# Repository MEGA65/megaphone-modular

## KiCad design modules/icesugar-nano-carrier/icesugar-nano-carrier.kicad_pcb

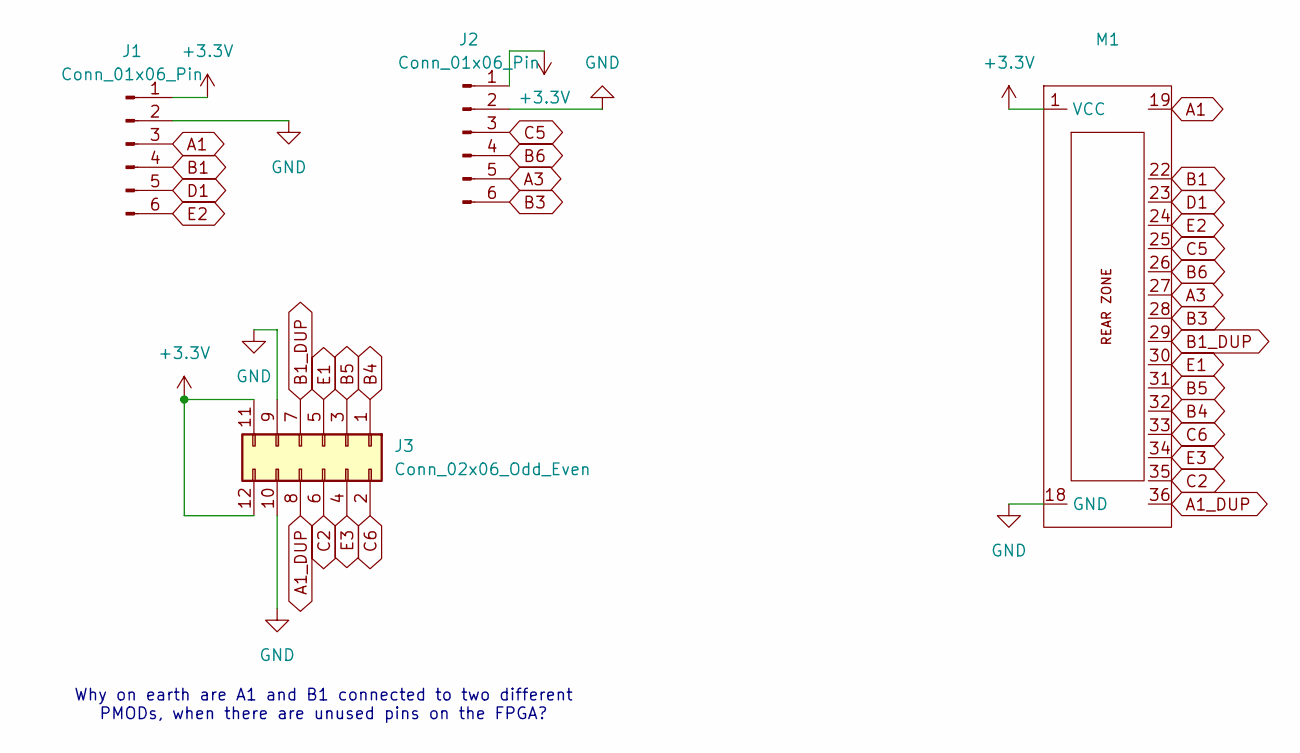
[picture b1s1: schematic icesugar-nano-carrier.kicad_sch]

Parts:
J1, J2: Conn_01x06_Pin; PinHeader_1x06_P2.54mm_Vertical
J3: Conn_02x06_Odd_Even; PinHeader_2x06_P2.54mm_Vertical
M1: MegaCastle2x18-Module-I24.0x40.9-M800067FFF

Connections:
+3.3V: J1.1, J2.1, J3.11, J3.12, M1.1 (VCC)
A1: J1.3, M1.19
A1_DUP: J3.8, M1.36
A3: J2.5, M1.27
B1: J1.4, M1.22
B1_DUP: J3.7, M1.29
B3: J2.6, M1.28
B4: J3.1, M1.32
B5: J3.3, M1.31
B6: J2.4, M1.26
C2: J3.6, M1.35
C5: J2.3, M1.25
C6: J3.2, M1.33
D1: J1.5, M1.23
E1: J3.5, M1.30
E2: J1.6, M1.24
E3: J3.4, M1.34
GND: J1.2, J2.2, J3.9, J3.10, M1.18 (GND)

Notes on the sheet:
Why on earth are A1 and B1 connected to two different PMODs, when there are unused pins on the FPGA?

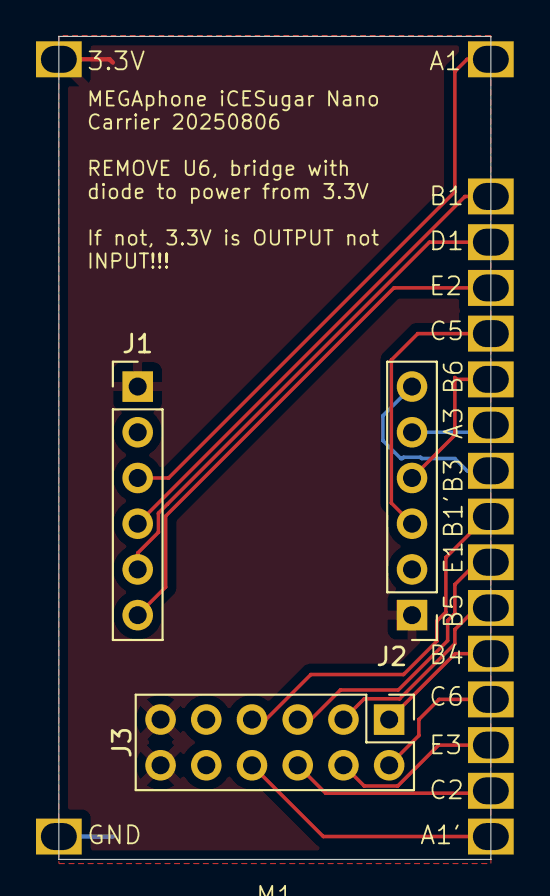
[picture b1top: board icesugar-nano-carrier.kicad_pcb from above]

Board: 2 copper layers, 24.0 x 45.7 mm, 4 parts (0 on the bottom side), 18 nets.

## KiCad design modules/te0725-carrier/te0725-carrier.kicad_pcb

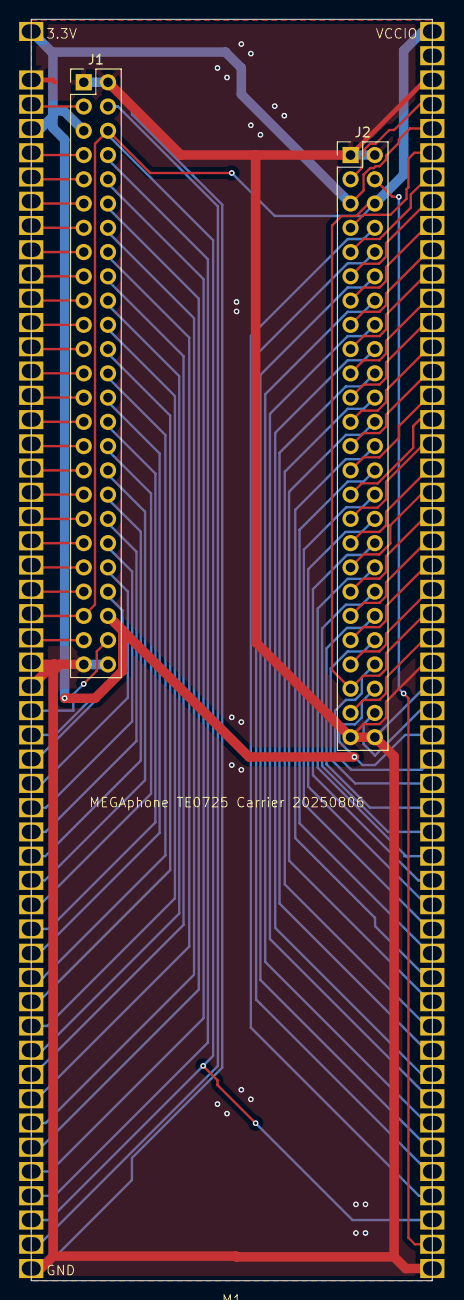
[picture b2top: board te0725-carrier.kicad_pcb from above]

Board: 2 copper layers, 42.0 x 132.1 mm, 3 parts (0 on the bottom side), 87 nets.

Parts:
J1, J2: Conn_02x25_Odd_Even; PinHeader_2x25_P2.54mm_Vertical
M1: MegaCastle2x52-Module-I42.0x127.3-M1

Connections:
J1_1: J1.1, J1.2, J1.49, J1.50, J2.1, J2.2, J2.49, J2.50, M1.3, M1.27, M1.28, M1.52 (GND), M1.55, M1.79, M1.80, M1.104
J1_3: J1.3, M1.4
J1_4: J1.4, M1.51
J1_7: J1.7, M1.6
J1_8: J1.8, M1.49
J1_9: J1.9, M1.7
J1_10: J1.10, M1.48
J1_11: J1.11, M1.8
J1_12: J1.12, M1.47
J1_13: J1.13, M1.9
J1_14: J1.14, M1.46
J1_15: J1.15, M1.10
J1_16: J1.16, M1.45
J1_17: J1.17, M1.11
J1_18: J1.18, M1.44
J1_19: J1.19, M1.12
J1_20: J1.20, M1.43
J1_21: J1.21, M1.13
J1_22: J1.22, M1.42
J1_23: J1.23, M1.14
J1_24: J1.24, M1.41
J1_25: J1.25, M1.15
J1_26: J1.26, M1.40
J1_27: J1.27, M1.16
J1_28: J1.28, M1.39
J1_29: J1.29, M1.17
J1_30: J1.30, M1.38
J1_31: J1.31, M1.18
J1_32: J1.32, M1.37
J1_33: J1.33, M1.19
J1_34: J1.34, M1.36
J1_35: J1.35, M1.20
J1_36: J1.36, M1.35
J1_37: J1.37, M1.21
J1_38: J1.38, M1.34
J1_39: J1.39, M1.22
J1_40: J1.40, M1.33
J1_41: J1.41, M1.23
J1_42: J1.42, M1.32
J1_43: J1.43, M1.24
J1_44: J1.44, M1.31
J1_45: J1.6, J1.45, J2.6, J2.45, M1.25, M1.50, M1.53, M1.77, M1.102
J1_46: J1.5, J1.46, J2.5, J2.46, M1.1 (VCC), M1.5, M1.30, M1.57, M1.82
J1_47: J1.47, M1.26
J1_48: J1.48, M1.29
J2_3: J2.3, M1.56
J2_4: J2.4, M1.103
J2_7: J2.7, M1.58
J2_8: J2.8, M1.101
J2_9: J2.9, M1.59
J2_10: J2.10, M1.100
J2_11: J2.11, M1.60
J2_12: J2.12, M1.99
J2_13: J2.13, M1.61
J2_14: J2.14, M1.98
J2_15: J2.15, M1.62
J2_16: J2.16, M1.97
J2_17: J2.17, M1.63
J2_18: J2.18, M1.96
J2_19: J2.19, M1.64
J2_20: J2.20, M1.95
J2_21: J2.21, M1.65
J2_22: J2.22, M1.94
J2_23: J2.23, M1.66
J2_24: J2.24, M1.93
J2_25: J2.25, M1.67
J2_26: J2.26, M1.92
J2_27: J2.27, M1.68
J2_28: J2.28, M1.91
J2_29: J2.29, M1.69
J2_30: J2.30, M1.90
J2_31: J2.31, M1.70
J2_32: J2.32, M1.89
J2_33: J2.33, M1.71
J2_34: J2.34, M1.88
J2_35: J2.35, M1.72
J2_36: J2.36, M1.87
J2_37: J2.37, M1.73
J2_38: J2.38, M1.86
J2_39: J2.39, M1.74
J2_40: J2.40, M1.85
J2_41: J2.41, M1.75
J2_42: J2.42, M1.84
J2_43: J2.43, M1.76
J2_44: J2.44, M1.83
J2_47: J2.47, M1.78
J2_48: J2.48, M1.81

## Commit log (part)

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2025-08-06 finish te0725 carrier module layout
2025-08-06 add symbols and footprints for ICESugar Nano module
2025-08-06 begin implementing iCESugar Nano carrier module
2025-08-10 begin making unicode string printer.
2025-08-10 display dimensions info for rendered string
2025-08-10 update icesugar project for gerber output
2025-08-10 remove debug stuff
2025-08-10 allow reverse text when rendering UTF8 strings
2025-08-10 reinstant use of colour emojis for UI font if required
2025-08-11 fix some padding bugs in text viewports
2025-08-11 fix padding bugs
2025-08-11 remove notes, try rendering reversed text
2025-08-16 use new BOLDISALT bit
2025-08-17 work towards displaying wrapped UTF8 strings
2025-08-20 work towards being able to natively compile all modules for SMS display
2025-08-20 get native build with all modules working
2025-08-20 get wrapped text display vaguely working
2025-08-20 get string breaking and wrapped display demonstration
2025-08-23 begin implementing mount calls
2025-08-29 add missing includes and sources for D81 routines
2025-08-30 fix fail() macro for native builds
2025-08-30 use ASCII not PETSCII for contacts.c
2025-08-30 get rid of vestical openfile calls
2025-08-30 fix sector buffer address type for native builds
2025-08-30 make sure we access the FDC buffer, not SD buffer
2025-08-30 test reading record from D81
2025-08-30 update libc, show reading first record on screen
2025-08-30 add record buffer for textbox handling
2025-08-30 fix bugs in rendering a text message body
2025-08-30 refactor out drawing of textbox.
2025-08-30 progress towards being able to place text boxes anywhere
2025-09-05 use RRB wraparound prevention
2025-09-05 progress towards showing SMS threads
2025-09-06 RRB wrap fix support etc.
2025-09-06 fix record_allocate_next() for native. show SMS thread.
2025-09-06 show SMS thread with sender and recipient messages
2025-09-06 logic for trimming message lines
2025-09-14 refactor SMS screen code into separate file
2025-09-16 begin work on sprite scroll bar
2025-09-20 get scroll bar rendering working
2025-09-20 remove old test code
2025-09-20 control sprite visibility for scroll bar
2025-09-20 implement cursor keys to scroll through SMS thread
2025-09-20 scrolling SMS threads works :)
2025-09-20 basic SMS message drafting with cursor keys and typing
2025-09-20 fix caching of draft message ling count
2025-09-20 try to save SMS draft after each edit
2025-09-20 begin implement native sector write routine
2025-09-20 read contact before retrieving message draft
2025-09-21 more work towards SMS sending
2025-09-25 progress towards using LLVM instead of CC65
2025-09-25 more LLVM work
2025-09-25 get it compiling with llvm, but not working yet
2025-09-27 fix llvm bugs
2025-09-28 fix llvm asm helper semantics etc
2025-09-28 implement llvm stack backtrace
2025-09-28 refine debug and backtrace stuff
2025-09-28 force initialisation of ZP rodata
2025-09-28 debug llvm SMS thread drawing
2025-09-28 ensure Z and D clear on entry
2025-09-28 tidy up and finish IRQ/BRK back tracing
2025-10-04 create dump file
2025-10-04 update import
2025-10-04 update linux cross compilation files
2025-10-04 correct common vs native source lists
2025-10-04 Revert "remove debug POKEs"
    This reverts commit 99a7b78cf16557add019c44e2ee9bd55dae675fa.
2025-10-04 remove all safe debug pokes
2025-10-05 generate linker repro.tar for mos-llvm debugging
2025-10-05 restore screen colour after trace stop
2025-10-05 flush key buffer on start
2025-10-05 remount conversation disk images after sending a message
2025-10-05 fix JSR return address calculation in backtrace
2025-10-05 fix arg order issue when sending SMS
2025-10-05 remove cursor before sending message
2025-10-05 fix drive selection for write_sector
2025-10-05 ... and for read_sector
2025-10-05 debug output when indexing
2025-10-05 resolve all compiler warnings with llvm
2025-10-06 activate "wait" sprite to show when busy
2025-10-06 animate "wait" indication
2025-10-06 fix empty string for sms draft rendering bugs
2025-10-06 fix more cursor handling bugs
2025-10-06 make cursor blink
2025-10-06 fix find cursor bug
2025-10-06 implement deleting of SMS messages
2025-10-06 begin work on dialpad glyph generator
2025-10-06 fix ASCII output for nybl packed pixels
2025-10-07 Make packed dialpad NCM glyphs
2025-10-07 add make target for dialpad NCM file
2025-10-07 pull in helper routines to load files from SD card
2025-10-07 plumb in dialer, remove duplicate helper-llvm.s
2025-10-07 progress towards showing dialer
2025-10-07 better align dialpad digits on buttons
2025-10-08 implement time on status bar, fix display glitches
2025-10-08 show phone signal strength
2025-10-08 tweak height of max signal bar
2025-10-08 push scroll bar down away from status bar
2025-10-08 adjust scroll bar colour and position
2025-10-08 finish paramaterising status bar element widths
2025-10-08 use full width of display for status bar
2025-10-08 refactor status bar segements to own functions
2025-10-11 begin work on contact display routine
2025-10-11 progress towards displaying contact info
2025-10-12 fix segfault risk
2025-10-12 fix various display glitches for contact + SMS thread
2025-10-12 implement left padding
2025-10-12 begin implementing movement between fields
2025-10-12 add dialpad to active field loop
2025-10-12 progress towards editing of all fields
2025-10-12 fix shift-TAB support
2025-10-12 more more screen paramaterisation to screen.h
2025-10-12 more work towards display and edit of all fields
2025-10-12 fix initial reading of contact
2025-10-12 fix some active field display bugs
2025-10-12 fix RRB wrap glitches
2025-10-12 more or less get af field retrieval etc working
2025-10-12 further paramatarise screen layout
2025-10-12 fix bugs with SMS message list scrolling
2025-10-12 improve safety straps for over-long fields
2025-10-12 fix bug with clear home on field
2025-10-12 in progress debugging field editing and saving
2025-10-13 remove debug output
2025-10-13 fix provisioning regression
2025-10-18 fix field editing bugs
2025-10-18 fix field drawing after delete
2025-10-18 fix contact field pixel pooh
2025-10-19 refactor UI controller code
2025-10-19 work towards contact list
2025-10-19 fix contact list scrolling bugs
2025-10-19 fix scroll bar for contact list
2025-10-19 fix switching back to SMS thread from contact list
2025-10-19 start in contact list
2025-10-19 fix SMS draft editing line count bug
2025-10-19 begin implementing create contact via +
2025-10-19 start on name field when creating a contact
2025-10-19 fix contact list extent handling after create contact
2025-10-26 create dialer emoji buttons
2025-10-26 complete rename to fonemain
2025-10-26 work on dialer buttons. use speak-no-evil for mute
2025-10-31 disable indexing to free up space
2025-11-01 show more dialier state
2025-11-01 work towards dialer info fields
2025-11-01 add back missing dialer strings
2025-11-01 dialpad active by default
2025-11-01 fix dialer string selection
2025-11-01 fix more rendering glitches
2025-11-01 hide DTMF history when not relevant
2025-11-01 work towards editing and cursor for dialer fields
2025-11-01 work on highlighting dialpad buttons when pressed
2025-11-01 get rid of dead debug code
2025-11-01 get dialpad highlighting working properly
2025-11-01 begin selecting which bits to include in binaries
2025-11-01 fix shared memory region handling problems
2025-11-01 refactor fone binary generation
2025-11-01 make simple init prog with all once-only code
2025-11-01 get foneinit compiling
2025-11-02 fix bugs with loader and foneinit
2025-11-02 add convenience make target for putting binaries onto SD card
2025-11-02 progress with separation of contact list and SMS thread progs
2025-11-03 more refactoring for separate progs
2025-12-07 make separate target to build SD binaries vs push them to SD card
2025-12-07 add target to push and run via FTP
2025-12-07 fix bugs with loading alternate executables
2025-12-07 begin renaming binaries
2025-12-07 fix buil;ding and pushing via ftp
2025-12-07 fix load chaining and reporting
2025-12-07 fix problems with glyph cache handling between programs
2025-12-07 update frame counter address to match moved shared state
2025-12-07 F1 = set dialer number
2025-12-07 progress towards call state management
2025-12-07 fix various bugs with F1 / dialing
2025-12-07 work on call state management, including timeouts
2025-12-07 fix call state timeouts and CLR of dialer string clearing contact name
2025-12-07 RETURN or SPACE to dial from contact list/dialer. Colours for buttons!
2025-12-07 update button colours when changing call state
2025-12-07 implement more call state. Blinking for mute button active
2025-12-07 rename blinky for power management
2025-12-07 begin populating and assigning pins
2025-12-11 plumb in power control uart rx
2025-12-11 work on bram
2025-12-12 get synthesising with BRAM
2025-12-12 work on playback of cellular log
2025-12-12 fix BRAM instantiation
2025-12-12 implement simple power control toggling
2025-12-12 parameterise UART speed. drop to 115.2K to keep icelink happy
2025-12-12 fix power switching and reporting bugs
2025-12-12 implement showing config message on ?
2025-12-13 simplify cel modem tap, add 2 more power circuits
2025-12-13 fix bugs with new circuits
2025-12-13 begin implementing powerctl demo program
2025-12-13 more thorough input flush
2025-12-13 progress towards reading circuit config fields
2025-12-13 begin parameterising field names
2025-12-13 fix more bugs with reading circuit info
2025-12-13 add further information to the config message
2025-12-13 add A-G commands to set cellular UART speed
2025-12-13 implement showing power control status
2025-12-13 implement get status, speed up config reads
2025-12-13 implement circuit switching commands
2025-12-13 debug +QIND and RING detection
2025-12-13 implement celplay command
2025-12-13 implement cellular uart speed selection
2025-12-13 further refinements. Log R for RING events
2025-12-13 document API. implement searching for circuit by name etc
2025-12-13 kill versioncheck sync bug once and for all. Hopefully.
2025-12-13 gracefully handle stuck low power button
2025-12-14 begin implementing cellular modem communications and test tool
2025-12-14 work on modem control module
2025-12-14 fix compilation errors
2025-12-14 implement SMS message count
2025-12-14 more work on SMS handling of cellular modem
2025-12-14 progress towards decoding and reading SMS
2025-12-14 more work on SMS decoder
2025-12-14 SMS decoder now works
2025-12-14 remove instrumentation and debug from SMS decoder
2025-12-14 begin work towards SMS encoding
2025-12-14 fix compiler warnings, progress towards sms sending
2025-12-14 fix handling of sending ESC on init to abort PDU entry
2025-12-14 fix emojis and other high-value unicode chars
2025-12-14 extra safety checks for splitting long emojified SMS
2025-12-16 add AI generated API summary
2025-12-16 implement smsnext command and API behind it
2025-12-27 refactor some routines out
2025-12-27 move modem test program to end of modem.c
2025-12-27 don't send AT commands while others in progress. Work on calling tone
2025-12-27 use TTS to keep caller informed of call progress
2025-12-27 add VoLTE detection
2025-12-28 add query function for cellular network name
2025-12-30 reduce debug output
2025-12-30 fix mega65 compilation errors
2025-12-30 pull in ASCII font for megacom
2025-12-30 add status bar
2025-12-30 work on options menu for megacom
2025-12-30 more work on megacom serial setup menus
2025-12-30 ack bytes received from buffered UART
2025-12-30 fix crashbugs in megaterm
2025-12-30 implement more basic terminal emulation features
2025-12-31 more megacom fixes
2025-12-31 fix mega65 compile error
2025-12-31 add missing return values in UART API
2026-01-01 add static check for shared structure size
2026-01-01 increase shared state size and add compile-time check
2026-01-01 revert back to 4KB shared structure
2026-01-01 progress towards showing cellular network time
2026-01-01 wire-in phone signal strength indication
2026-01-01 fix parsing of call state indications
2026-01-01 implement RETURN to answer or hangup.
2026-01-01 update call state display when hanging up
2026-01-01 detect calls without caller ID present
2026-01-01 fix handling of calls with no caller ID
